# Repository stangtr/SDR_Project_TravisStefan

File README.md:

# SDR_Project_TravisStefan

## Project Overview
The goal of this project was to design a Software Defined Reciever (SDR) for ENGR 357 Electronics II at Walla Walla University.
Our receiver is designed for the AM frequency range (535kHz - 1605kHz).
Before designing the board in KiCad, we did some simulations in LTSpice to find the correct values for resistors and capacitors, as well as inductors for the band-pass filter (BPF).

## Finished Product
Ideally, the SDR board would have a signal input to the female SMA connector on the input of the BPF. This signal would then be processed and sent to the computer via an auxiliary cable. The correct frequency could be tuned to using the Quisk open radio software. An Arduino is connected to the board for powering the ICs and setting the correct clock output on the Si5351 oscillator IC through communication with Quisk or a short test program. 

## More Documentation
More details can be viewed about the process and the specifications in the wiki tab.

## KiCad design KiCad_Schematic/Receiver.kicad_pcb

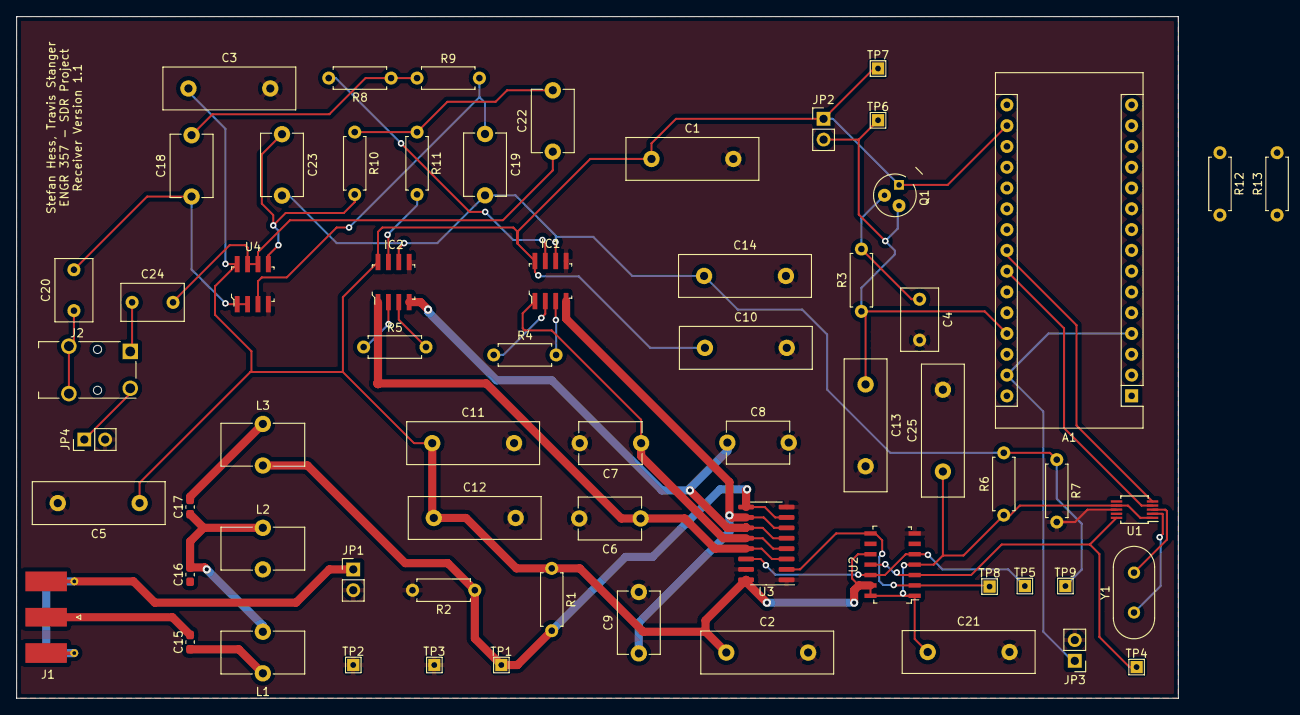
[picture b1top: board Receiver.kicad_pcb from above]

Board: 2 copper layers, 142.0 x 83.3 mm, 65 parts (0 on the bottom side), 39 nets.

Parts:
A1: Arduino_Nano_v3.x; Arduino_Nano
C1, C2, C3, C5, C10, C11, C12, C13, C14, C21, C25: .1u; C_Disc_D16.0mm_W5.0mm_P10.00mm
C4, C20, C24: 10u; C_Disc_D7.5mm_W4.4mm_P5.00mm
C6, C7, C8, C9: 750p; C_Disc_D7.5mm_W5.0mm_P7.50mm
C15, C17: 4.3n; C_0603_1608Metric_Pad1.05x0.95mm_HandSolder
C16: 5.1n; C_0603_1608Metric_Pad1.05x0.95mm_HandSolder
C18, C22: 220p; C_Disc_D7.5mm_W5.0mm_P7.50mm
C19, C23: 100p; C_Disc_D7.5mm_W5.0mm_P7.50mm
IC1, IC2: INA821ID; SOIC-8_W3.9mm
J1: Input (From Antenna); SMA_Molex_73251-1153_EdgeMount_Horizontal
J2: Aux. Out (to comp.); Jack_3.5mm_Switronic_ST-005-G_horizontal
JP1: Input_GND; PinHeader_1x02_P2.54mm_Vertical
JP2: Smooth_4.3; PinHeader_1x02_P2.54mm_Vertical
JP3: Ard_GND; PinHeader_1x02_P2.54mm_Vertical
JP4: Aux_GND; PinHeader_1x02_P2.54mm_Vertical
L1, L3: 6.2u; L_Toroid_Vertical_L10.0mm_W5.0mm_P5.08mm
L2: 5.1u; L_Toroid_Vertical_L10.0mm_W5.0mm_P5.08mm
Q1: 2N2222ACS-ND; TO-18-3
R1, R2: 10k; R_Axial_DIN0207_L6.3mm_D2.5mm_P7.62mm_Horizontal
R3, R6, R7: 1k; R_Axial_DIN0207_L6.3mm_D2.5mm_P7.62mm_Horizontal
R4, R5: 100; R_Axial_DIN0207_L6.3mm_D2.5mm_P7.62mm_Horizontal
R8, R11: 8.2k; R_Axial_DIN0207_L6.3mm_D2.5mm_P7.62mm_Horizontal
R9, R10: 15k; R_Axial_DIN0207_L6.3mm_D2.5mm_P7.62mm_Horizontal
R12, R13: 2.2k; R_Axial_DIN0207_L6.3mm_D2.5mm_P7.62mm_Horizontal
TP1: GND_2.5; TestPoint_THTPad_1.5x1.5mm_Drill0.7mm
TP2, TP3: GND_Pt; TestPoint_THTPad_1.5x1.5mm_Drill0.7mm
TP4: Clk0; TestPoint_THTPad_1.5x1.5mm_Drill0.7mm
TP5: I_LO; TestPoint_THTPad_1.5x1.5mm_Drill0.7mm
TP6: +5V; TestPoint_THTPad_1.5x1.5mm_Drill0.7mm
TP7: +4.3V; TestPoint_THTPad_1.5x1.5mm_Drill0.7mm
TP8: Q_LO; TestPoint_THTPad_1.5x1.5mm_Drill0.7mm
TP9: Ref_2.5; TestPoint_THTPad_1.5x1.5mm_Drill0.7mm
U1: Si5351A-B-GT; MSOP-10_3x3mm_P0.5mm
U2: SN74AC74DR; SOIC-14_W3.9mm
U3: SN74CBT3253C; SOIC-16_3.9x9.9mm_P1.27mm
U4: LM358DR; SOIC-8_W3.9mm
Y1: Crystal; Crystal_HC49-U_Vertical

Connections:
+3V3: A1.17, C1.1, C2.1, C3.1, C12.1, R12.1, R13.2, U1.1, U1.7, U2.1, U2.4, U2.10, U2.13, U2.14
+4.3V_S: C5.1, C10.1, C11.1, C21.1, C25.1, IC1.8, IC2.8, JP2.1, Q1.1, R1.1, R6.1, TP7.1, U3.16, U4.8
+5V: A1.27, C13.1, JP2.2, Q1.3, R3.1, TP6.1
/0: C9.1, IC1.4, U3.6, U3.10
/90: C8.1, IC2.4, U3.5, U3.11
/180: C7.1, IC1.1, U3.4, U3.12
/270: C6.1, IC2.1, U3.3, U3.13
/GND_2.5: L3.2, R1.2, R2.1, TP1.1, U3.7, U3.9
/I_LO: TP5.1, U2.5, U2.12, U3.14
/I_sig: C20.1, J2.T
/I_sig_O: IC1.7, R8.2
/Q_LO: TP8.1, U2.2, U2.8, U3.2
/Q_sig: C24.1, J2.R
/Q_sig_O: IC2.7, R11.2
/Ref_2.5: C14.1, C19.2, C23.2, IC1.6, IC2.6, R6.2, R7.1, TP9.1
/SCL: A1.24, R12.2, U1.4
/SDA: A1.23, R13.1, U1.5
GND: C1.2, C2.2, C3.2, C4.2, C5.2, C6.2, C7.2, C8.2, C9.2, C10.2, C11.2, C12.2, C13.2, C14.2, C21.2, C25.2, IC1.5, IC2.5, JP1.2, JP3.2, JP4.2, R2.2, R7.2, TP2.1, TP3.1, U1.8, U2.7, U3.1, U3.8, U3.15, U4.4
unnamed: A1.4, A1.29, JP3.1
unnamed: C4.1, Q1.2, R3.2
unnamed: C15.1, L1.1
unnamed: C15.2, J1.1
unnamed: C16.1, J1.2, JP1.1, L2.2
unnamed: C16.2, C17.1, L1.2, L2.1
unnamed: C17.2, L3.1
unnamed: C18.1, C20.2, U4.1, U4.2
unnamed: C18.2, R8.1, R9.1
unnamed: C19.1, R9.2, U4.3
unnamed: C22.1, C24.2, U4.6, U4.7
unnamed: C22.2, R10.1, R11.1
unnamed: C23.1, R10.2, U4.5
unnamed: IC1.2, R4.1
unnamed: IC1.3, R4.2
unnamed: IC2.2, R5.1
unnamed: IC2.3, R5.2
unnamed: J2.S, JP4.1
unnamed: TP4.1, U1.10, U2.3, U2.11
unnamed: U1.2, Y1.1
unnamed: U1.3, Y1.2

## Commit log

2020-06-08 Some stuff change (auto-save)
2020-06-08 (auto-save)
2020-06-08 Moved BlockDiagram
2020-06-08 Added New Schematic Picture
2020-06-08 Added Arduino Code
2020-06-09 Added KiCad Files and Libraries
2020-06-09 Added LTSpice Simulation Files
2020-06-09 Added PCB and Oscilloscope Images
2020-06-09 Added Pictures to the file OscilloscopeImages_TravisS
2020-06-10 Added Stefan's image folder
2020-06-10 Added my Oscilloscope Images
2020-06-10 Added BOM in the awesome flavors of csv and ods!
2020-06-10 Added some images
